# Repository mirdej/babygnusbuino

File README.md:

babygnusbuino
=============

minimal arduino compatible usb dongle based on the gnusb

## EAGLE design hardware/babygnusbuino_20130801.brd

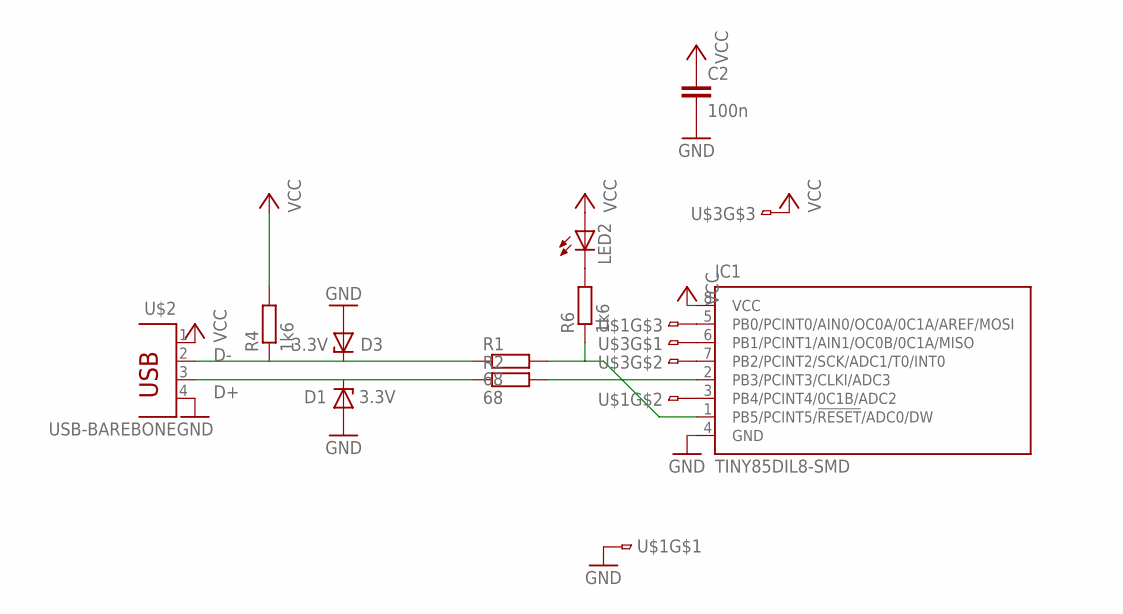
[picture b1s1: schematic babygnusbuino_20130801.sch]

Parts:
C2: 100n; C1206
D1, D3: 3.3V; SOD80C
IC1: TINY85DIL8-SMD; DIL08_SMD
LED2: LEDKA-3528ASYC; KA-3528ASYC
R1, R2: 68; R1206
R4, R6: 1k6; R1206
U$1, U$3: 3PIN-SMD-2.54
U$2: USB-BAREBONE

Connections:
D+: D1.C, R2.1, U$2.3 (D+)
D-: D3.C, R1.1, R4.1, U$2.2 (D-)
GND: C2.2, D1.A, D3.A, IC1.4 (GND), U$1.1, U$2.4 (GND)
unnamed: IC1.2 (PB3/PCINT3/CLKI/ADC3), R2.2
unnamed: IC1.1 (PB5/PCINT5/!RESET!/ADC0/DW), R1.2, R6.1
unnamed: IC1.3 (PB4/PCINT4/0C1B/ADC2), U$1.2
unnamed: IC1.5 (PB0/PCINT0/AIN0/OC0A/0C1A/AREF/MOSI), U$1.3
unnamed: IC1.6 (PB1/PCINT1/AIN1/OC0B/0C1A/MISO), U$3.1
unnamed: IC1.7 (PB2/PCINT2/SCK/ADC1/T0/INT0), U$3.2
unnamed: LED2.C, R6.2
VCC: C2.1, IC1.8 (VCC), LED2.A, R4.2, U$2.1 (VBUS), U$3.3

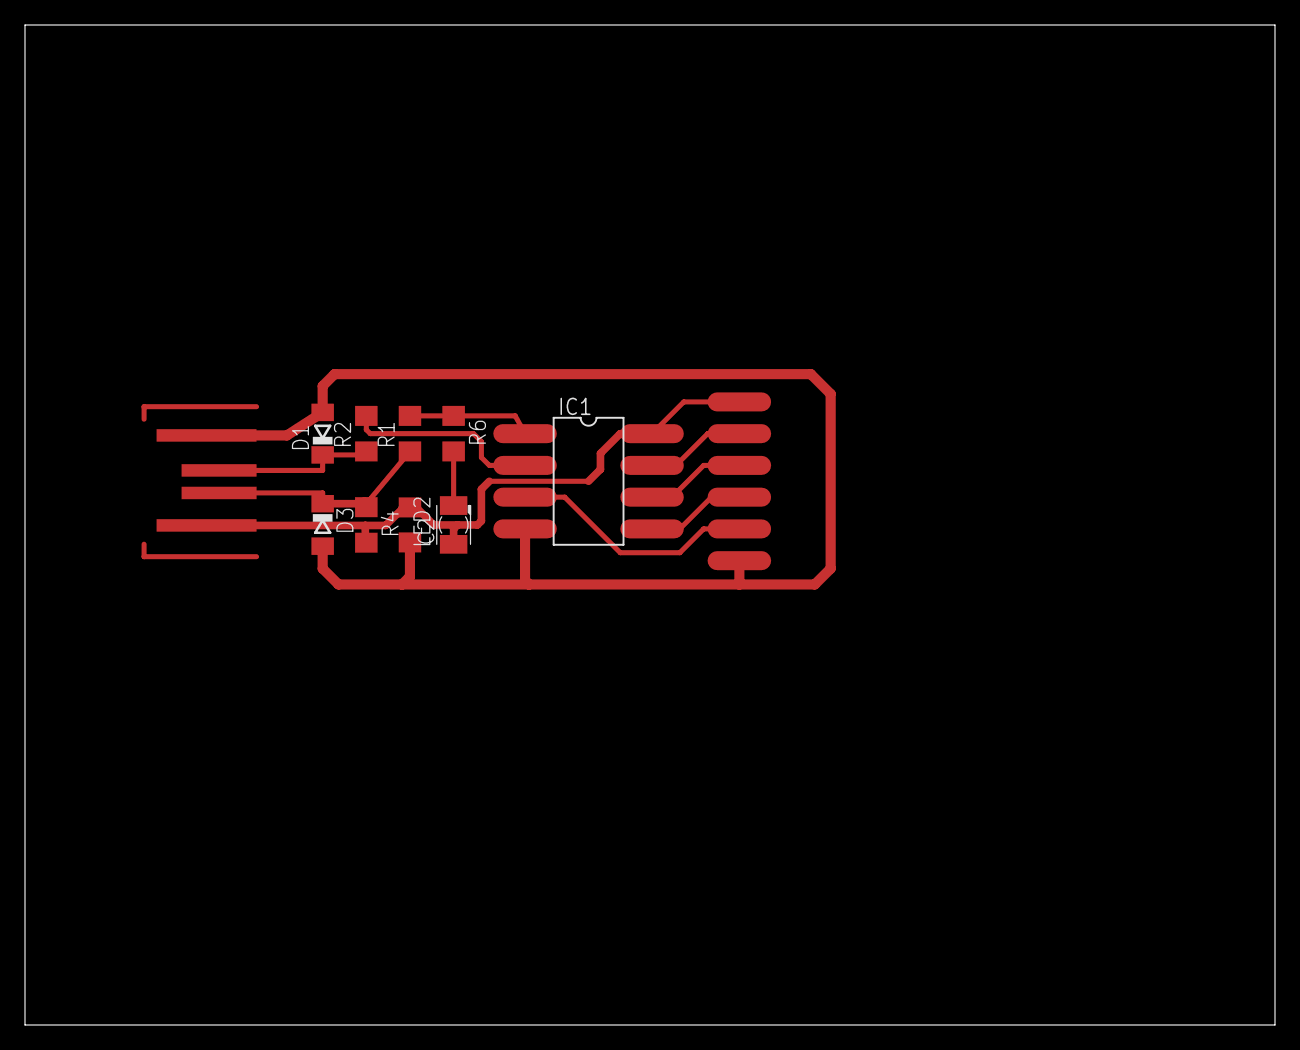
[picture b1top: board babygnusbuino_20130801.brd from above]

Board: 2 copper layers, 100.0 x 80.0 mm, 12 parts (0 on the bottom side), 11 nets.

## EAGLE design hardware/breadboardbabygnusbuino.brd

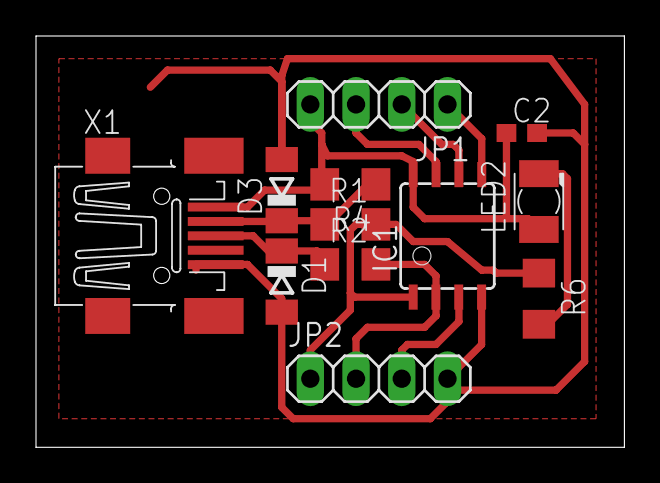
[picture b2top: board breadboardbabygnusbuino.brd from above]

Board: 2 copper layers, 32.7 x 22.9 mm, 12 parts (0 on the bottom side), 11 nets.

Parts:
C2: 100n; C0603
D1, D3: 3.3V; SOD80C
IC1: TINY85-20SU; 8S2
JP1, JP2: 1X04
LED2: KA-3528ASYC
R1, R2: 68; R1206
R4, R6: 1k6; R1206
X1: MINI-USB-32005-201; 32005-201

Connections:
D+: D1.C, R2.1, X1.3
D-: D3.C, R1.1, R4.1, X1.2
GND: C2.2, D1.A, D3.A, IC1.4, JP2.4, X1.5
unnamed: IC1.2, JP2.2, R2.2
unnamed: IC1.1, JP2.1, R1.2, R6.1
unnamed: IC1.7, JP1.3
unnamed: IC1.6, JP1.2
unnamed: IC1.3, JP2.3
unnamed: IC1.5, JP1.1
unnamed: LED2.C, R6.2
VCC: C2.1, IC1.8, JP1.4, LED2.A, R4.2, X1.1

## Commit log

2013-05-10 added ignore file
2013-05-11 removed some compiler errors, added 3rd PWM
2013-05-11 added midi support
2013-05-11 second prototype board version
2013-05-11 added device connect/disconnect pullup support on PB2
2013-05-11 pullup control for usb device connect/disconnect is not needed. another free pin for midi stuff
2013-05-12 added so8 version
2013-05-12 bug in wdt_disable()? that prevented gnubl from working
2013-05-12 added newest avrdude uspasp patch
2013-05-12 renamed midi library to GnusbuinoMIDI, jump to bootloader using watchdog timer, renamed device descriptor to babygnusbuino
2013-05-12 changed analog pin definition mechanism
2013-05-13 added port description figures
2013-06-15 added bootloader hex file
2013-06-15 modified fuses in boards.tx to reflect makefile of bootloader
2013-07-30 added gif of schematic. cosmetics on board
2013-07-30 first version of breadboardbabygnusbuino
2013-07-31 switched programmer back to usbasp
2013-07-31 removed segmentation fault error in avrdude patch. removed duplicate entries in boards.txt
2013-07-31 added more sleep
2013-07-31 added patched avrdude (v6.0rc1) for linux
2013-07-31 added avrdude binary for mac
2013-07-31 added avrdude.conf file
2013-07-31 added avrdude.conf for mac
2013-07-31 added install script
2013-07-31 added instal script for mac
2013-08-01 added new reference design
2013-08-01 replaced avrdude with static version for users without libusb :P
2013-08-01 added libusb for binary mac distribution
2013-08-01 added both eeded dylibs
2013-08-02 added standard mac installer package for avrdude-patch
2013-08-02 removed evil libSystem.B.dylib from installer package
2013-08-02 removed dangerous installer package
2013-08-02 returned avrdude binary
2014-09-14 changed files to make them compatible with gcc 4.9.0, commented #define BIN for compatibility.
2015-04-22 migrated structure to arduino 1.5.x and later versions
2015-04-22 gcc wants some vars to be static
2015-04-22 removed hacky install script
2015-04-22 added avrdude
2015-04-22 removed outdated avrdude and avrdude.conf for linux
2015-04-22 updated boards and platform to use the hacked avrdude, only linux supported. user still has to manually put a hacked copy of avrdude.
2015-04-22 re-added empty linux folder
2015-04-22 fixed includes to reflect new GnusbuinoMIDI library structure
2015-05-20 added usbtiny programmer
2015-05-20 bug fixed ADLAR -> ADMUX register
2015-05-20 fixed admuxmask length
